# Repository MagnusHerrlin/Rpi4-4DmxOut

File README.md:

A prototype board to get four isolated dmx outputs from a raspberry pi 4
to use with ola https://github.com/OpenLightingProject/ola and the UART native DMX plugin.

I used Matthias Hertels design from here: http://mathertel.de/Arduino/DMXShield.aspx and modified it.

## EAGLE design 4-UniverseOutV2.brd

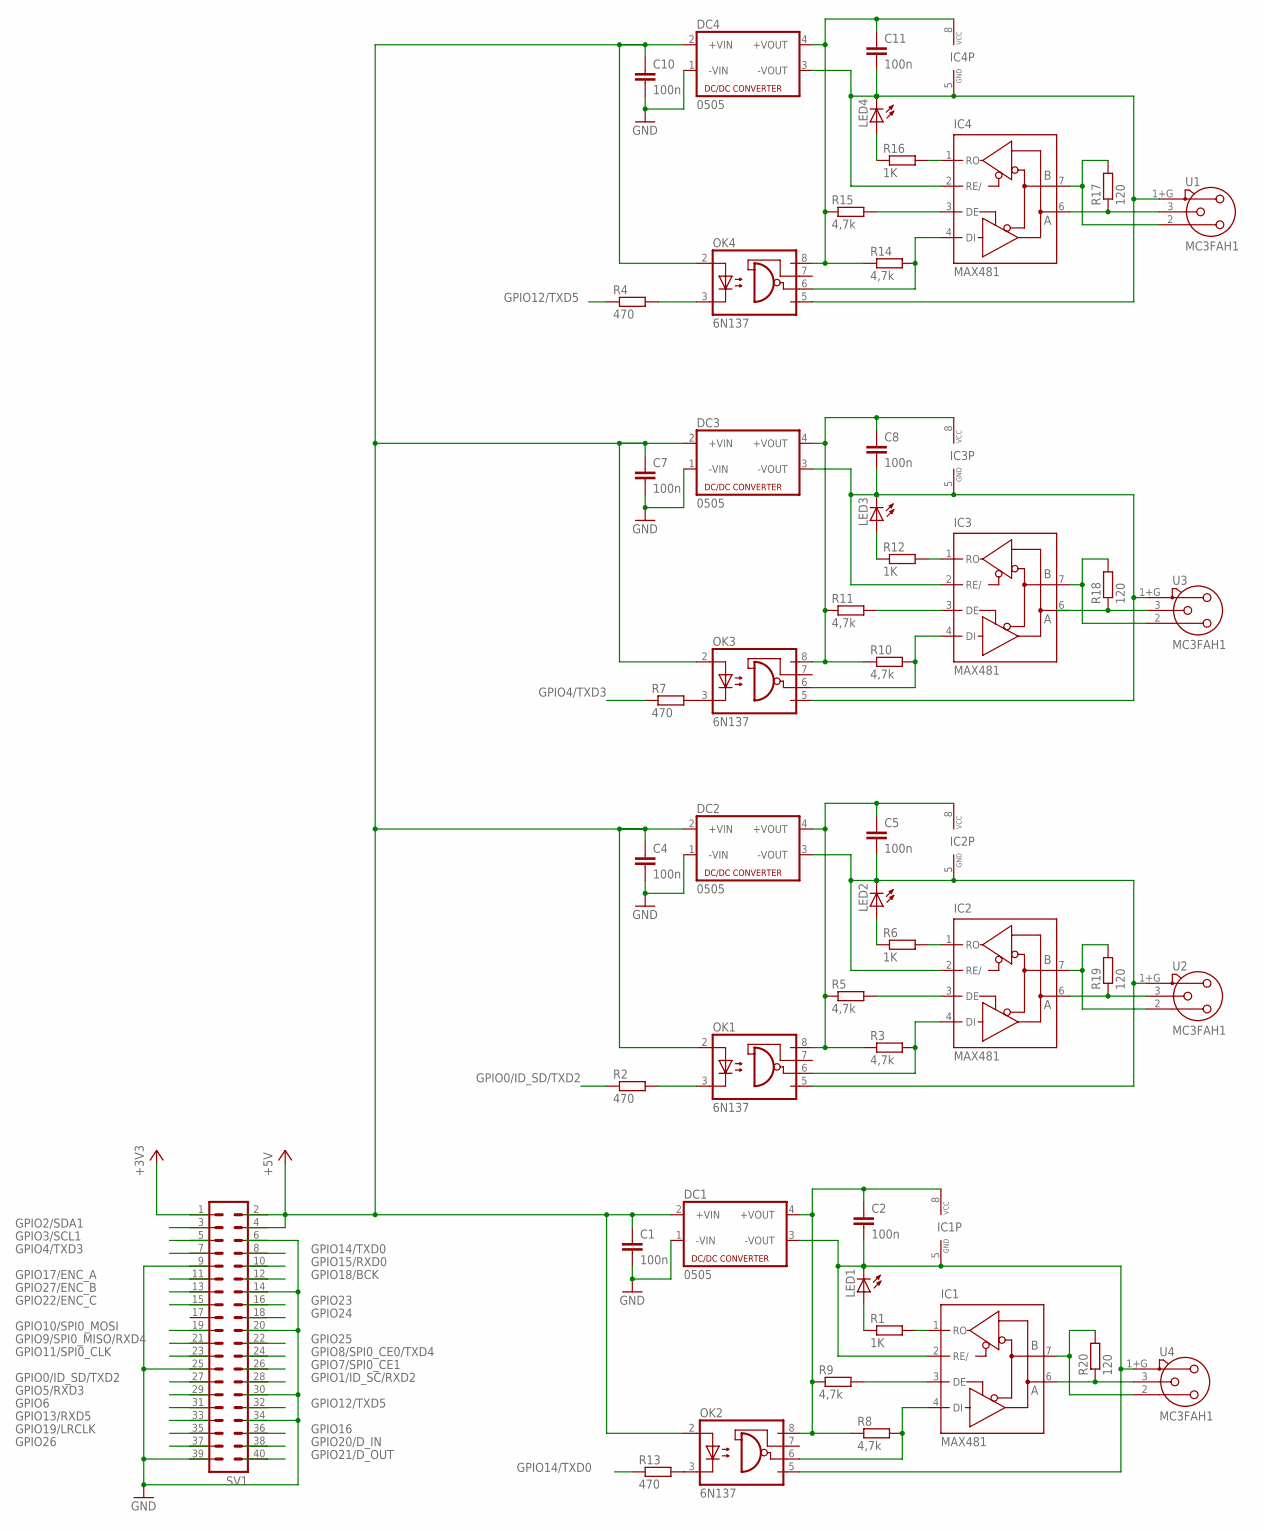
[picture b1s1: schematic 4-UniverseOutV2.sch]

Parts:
C1, C4, C7, C10: 100n; C5B3
C2, C5, C8, C11: 100n; C7.5B3
DC1, DC2, DC3, DC4: 0505; NME
IC1, IC2, IC3, IC4: MAX481; DIL08
LED1, LED2, LED3, LED4: LED3MM
OK1, OK2, OK3, OK4: 6N137; DIL08
R1, R6, R12, R16: 1K; 0204/7
R2, R4, R7, R13: 470; 0204/7
R3, R5, R8, R9, R10, R11, R14, R15: 4,7k; 0204/7
R17, R18, R19, R20: 120; 0207/2V
SV1: ML40
U1, U2, U3, U4: MC3FAH1; NC3FAH1

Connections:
+3V3: SV1.1
+5V: C1.1, C4.1, C7.1, C10.1, DC1.2 (+VIN), DC2.2 (+VIN), DC3.2 (+VIN), DC4.2 (+VIN), OK1.2 (A), OK2.2 (A), OK3.2 (A), OK4.2 (A), SV1.2, SV1.4
+5V_EXT: C2.1, DC1.4 (+VOUT), IC1.8 (VCC), OK2.8 (VCC), R8.1, R9.1
+5V_EXT1: C5.1, DC2.4 (+VOUT), IC2.8 (VCC), OK1.8 (VCC), R3.1, R5.1
+5V_EXT2: C8.1, DC3.4 (+VOUT), IC3.8 (VCC), OK3.8 (VCC), R10.1, R11.1
+5V_EXT3: C11.1, DC4.4 (+VOUT), IC4.8 (VCC), OK4.8 (VCC), R14.1, R15.1
GND: C1.2, C4.2, C7.2, C10.2, DC1.1 (-VIN), DC2.1 (-VIN), DC3.1 (-VIN), DC4.1 (-VIN), SV1.6, SV1.9, SV1.14, SV1.20, SV1.25, SV1.30, SV1.34, SV1.39
GND_EXT: C2.2, DC1.3 (-VOUT), IC1.2 (RE/), IC1.5 (GND), LED1.K (C), OK2.5 (GND), U4.1+G (1)
GND_EXT1: C5.2, DC2.3 (-VOUT), IC2.2 (RE/), IC2.5 (GND), LED2.K (C), OK1.5 (GND), U2.1+G (1)
GND_EXT2: C8.2, DC3.3 (-VOUT), IC3.2 (RE/), IC3.5 (GND), LED3.K (C), OK3.5 (GND), U3.1+G (1)
GND_EXT3: C11.2, DC4.3 (-VOUT), IC4.2 (RE/), IC4.5 (GND), LED4.K (C), OK4.5 (GND), U1.1+G (1)
GPIO0/ID_SD/TXD2: R2.1, SV1.27
GPIO1/ID_SC/RXD2: SV1.28
GPIO2/SDA1: SV1.3
GPIO3/SCL1: SV1.5
GPIO4/TXD3: R7.1, SV1.7
GPIO5/RXD3: SV1.29
GPIO6: SV1.31
GPIO7/SPI0_CE1: SV1.26
GPIO8/SPI0_CE0/TXD4: SV1.24
GPIO9/SPI0_MISO/RXD4: SV1.21
GPIO10/SPI0_MOSI: SV1.19
GPIO11/SPI0_CLK: SV1.23
GPIO12/TXD5: R4.1, SV1.32
GPIO13/RXD5: SV1.33
GPIO14/TXD0: R13.1, SV1.8
GPIO15/RXD0: SV1.10
GPIO16: SV1.36
GPIO17/ENC_A: SV1.11
GPIO18/BCK: SV1.12
GPIO19/LRCLK: SV1.35
GPIO20/D_IN: SV1.38
GPIO21/D_OUT: SV1.40
GPIO22/ENC_C: SV1.15
GPIO23: SV1.16
GPIO24: SV1.18
GPIO25: SV1.22
GPIO26: SV1.37
GPIO27/ENC_B: SV1.13
unnamed: OK4.3 (C), R4.2
unnamed: OK3.3 (C), R7.2
unnamed: OK1.3 (C), R2.2
unnamed: OK2.3 (C), R13.2
unnamed: IC1.3 (DE), R9.2
unnamed: IC1.4 (DI), OK2.6 (VO), R8.2
unnamed: IC1.6 (A), R20.1, U4.3
unnamed: IC1.7 (B), R20.2, U4.2
unnamed: IC1.1 (RO), R1.2
unnamed: LED1.A, R1.1
unnamed: IC2.3 (DE), R5.2
unnamed: IC2.4 (DI), OK1.6 (VO), R3.2
unnamed: IC2.6 (A), R19.1, U2.3
unnamed: IC2.7 (B), R19.2, U2.2
unnamed: IC2.1 (RO), R6.2
unnamed: LED2.A, R6.1
unnamed: IC3.3 (DE), R11.2
unnamed: IC3.4 (DI), OK3.6 (VO), R10.2
unnamed: IC3.6 (A), R18.1, U3.3
unnamed: IC3.7 (B), R18.2, U3.2
unnamed: IC3.1 (RO), R12.2
unnamed: LED3.A, R12.1
unnamed: IC4.3 (DE), R15.2
unnamed: IC4.4 (DI), OK4.6 (VO), R14.2
unnamed: IC4.6 (A), R17.1, U1.3
unnamed: IC4.7 (B), R17.2, U1.2
unnamed: IC4.1 (RO), R16.2
unnamed: LED4.A, R16.1

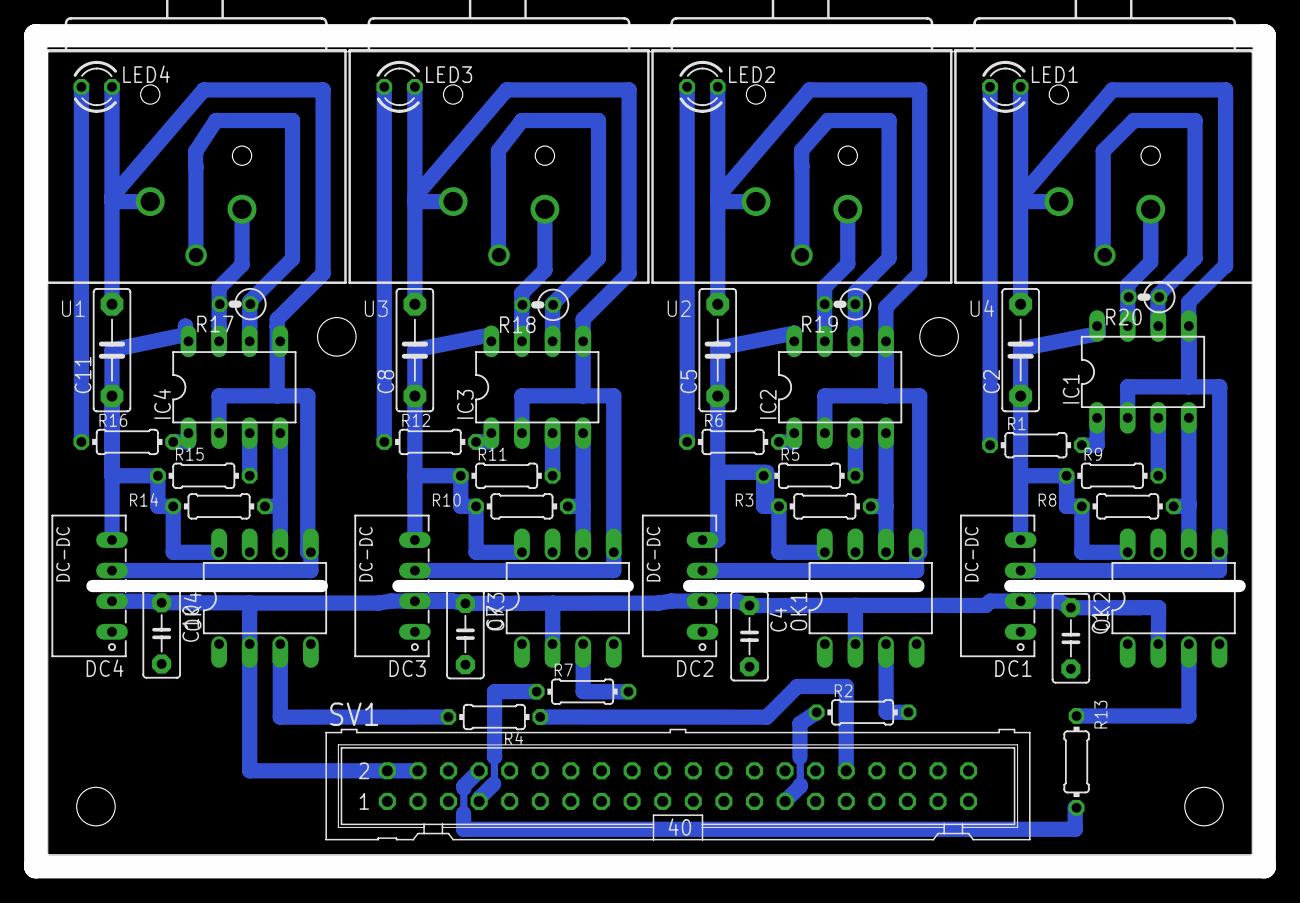
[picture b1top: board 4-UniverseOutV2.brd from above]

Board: 2 copper layers, 102.0 x 69.0 mm, 49 parts (0 on the bottom side), 42 nets.

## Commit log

2020-12-21 Create Eagle
2020-12-22 Create ola-uartdmx.conf
    Replace /etc/ola/ola-uartdmx.conf with this to enable RPI4 extra uarts
2020-12-22 Add files via upload
    Added 120ohm resistors
